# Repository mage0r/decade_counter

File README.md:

Attiny 85 Decade Counter
=============

This project puts an attiny 85 and a neopixel into a decade counter.

The decade counter in question is available from adafruit (http://www.adafruit.com/products/1082 "Mechanical Decade Counters").  Each stock counter has 10 pins and a common ground, with this replacement board the values can be read using an i2c connection on a common bus.

There are three sections, the circuit design for kicad, an arduino sketch with some awful code in it and lastly a few photos of the finished product.

The neopixel was included to hopefully shine some rgb light out the viewing window.  However in practice this light can't be seen.  3D printing a replacement dial is the next step in this project.

CREDITS
------------
This project was designed by John Spencer - john.spencer.9000@gmail.com - https://github.com/mage0r

SPECIAL THANKS
------------

To the HackMelbourne (CCHS, http://hackmelbourne.org) community of Melbourne, Australia.

To all other open-source developers whose countless hours supported every other aspect of this design.

DISTRIBUTION
------------
The specific terms of distribution of this project are governed by the
license referenced below. Please contact the copyright owner if you wish to modify the board for distribution. Please utilize this design for personal or research projects. Please acknowledge all contributors.

LICENSE
-------
Licensed under the TAPR Open Hardware License (www.tapr.org/OHL).
The "license" sub-folder also contains a copy of this license in plain text format.

Copyright John Spencer 2014
john.spencer.9000@gmail.com

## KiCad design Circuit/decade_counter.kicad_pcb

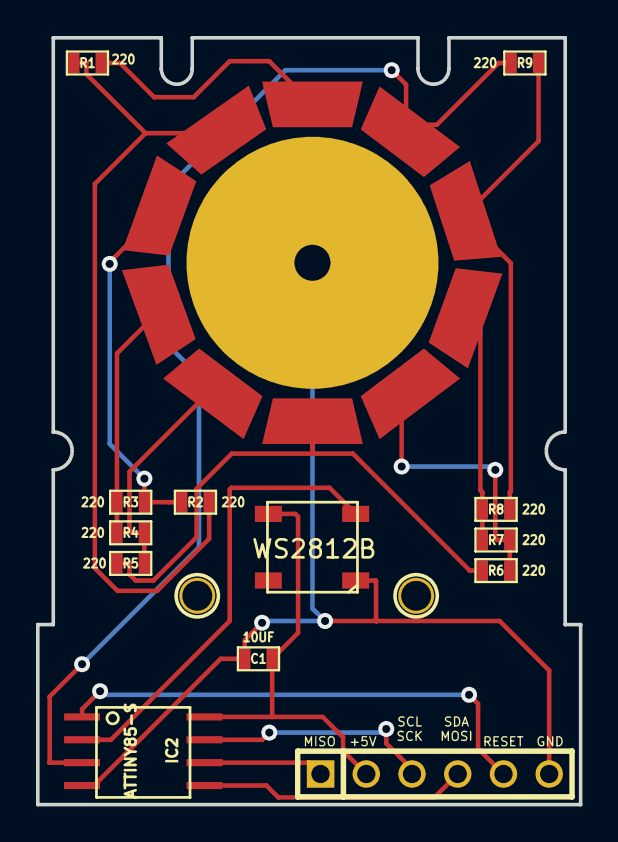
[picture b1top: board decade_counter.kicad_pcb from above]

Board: 2 copper layers, 30.2 x 42.6 mm, 26 parts (0 on the bottom side), 17 nets.

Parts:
C1: 10UF; SM0603
IC1: WS2812B; ws2812b
IC2: ATTINY85-S; SOIC8_W
P1: POS_9; position
P2: POS_8; position
P3: POS_7; position
P4: POS_6; position
P5: POS_5; position
P6: POS_4; position
P7: POS_3; position
P8: POS_2; position
P9: POS_1; position
P10: POS_0; position
P11: CONN_3X2; PIN_ARRAY-6X1
P12: Rail
R1, R2, R3, R4, R5, R6, R7, R8, R9: 220; SM0603
holes: hole_1; holes
holes2: hole_2; holes

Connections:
+5V: C1.1, IC1.1, IC2.8, P11.2
GND: C1.2, IC1.3, IC2.4, P11.6, P12.1
unnamed: P4.1, R3.2, R4.2
unnamed: P3.1, R2.1, R3.1
unnamed: P2.1, R1.2, R2.2
unnamed: P5.1, R4.1, R5.1
unnamed: P6.1, R5.2, R6.2
unnamed: P7.1, R6.1, R7.1
unnamed: P8.1, R7.2, R8.2
unnamed: IC2.6, P11.1
unnamed: IC2.5, P11.4
unnamed: IC2.1, P11.5
unnamed: IC2.7, P11.3
unnamed: P1.1, R1.1
unnamed: P9.1, R8.1, R9.1
unnamed: IC2.3, P10.1, R9.2
unnamed: IC1.4, IC2.2

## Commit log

2014-05-25 Initial commit, readme, circuit and sketch
2014-05-25 fixed typo
2014-05-25 good grief
2014-06-01 Added license
